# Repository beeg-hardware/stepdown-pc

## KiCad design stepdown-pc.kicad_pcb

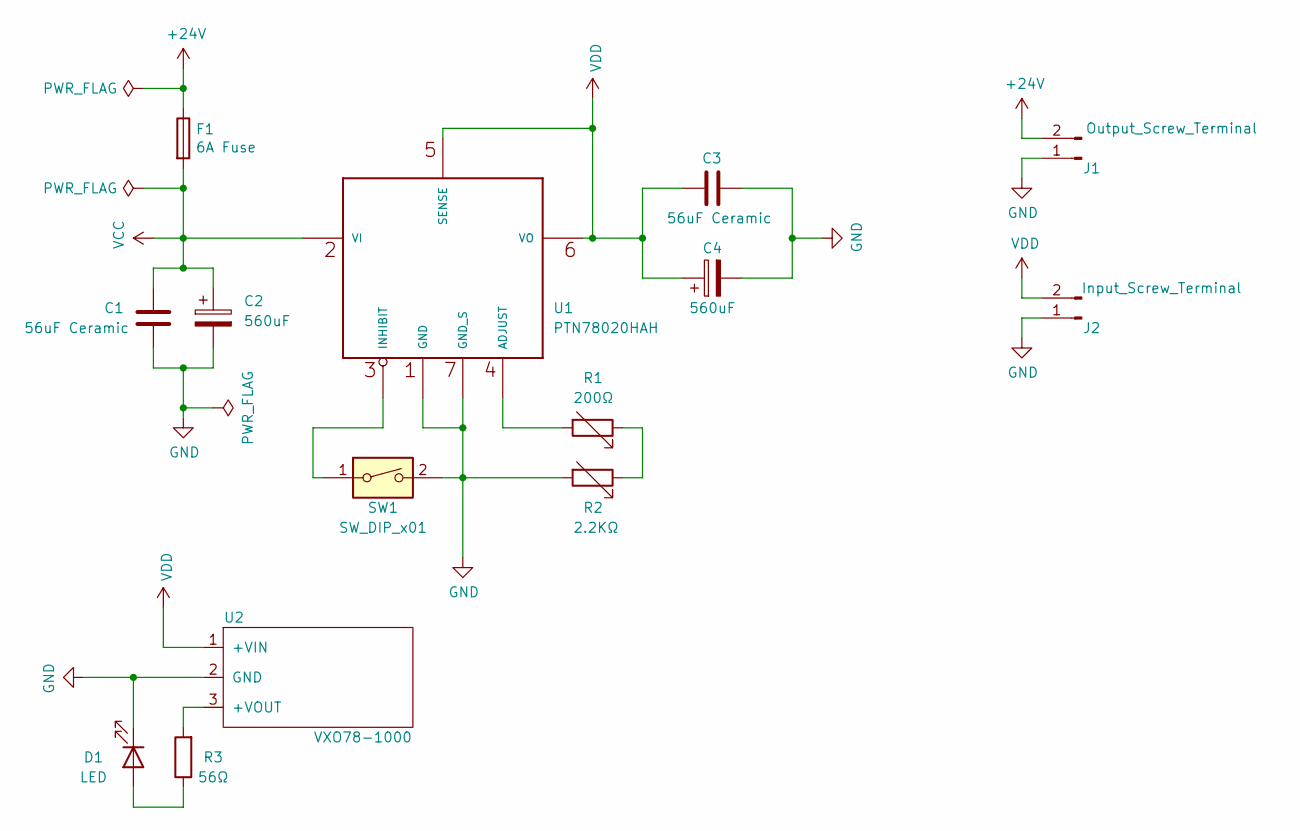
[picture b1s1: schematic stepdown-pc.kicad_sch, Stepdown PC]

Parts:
C1, C3: 56uF Ceramic; C_Rect_L7.0mm_W3.5mm_P5.00mm
C2, C4: 560uF; CP_Radial_D18.0mm_P7.50mm
D1: LED; LED_Rectangular_W3.0mm_H2.0mm
F1: 6A Fuse; Fuseholder_Cylinder-5x20mm_Littlelfuse_520_Horizontal_Open
J1: Output_Screw_Terminal; PhoenixContact_MSTBA_2,5_2-G-5,08_1x02_P5.08mm_Horizontal
J2: Input_Screw_Terminal; PhoenixContact_MSTBA_2,5_2-G-5,08_1x02_P5.08mm_Horizontal
R1: 200Ω; Potentiometer_Piher_Amphenol_PT-10-V10_Vertical_Hole
R2: 2.2KΩ; Potentiometer_Piher_Amphenol_PT-10-V10_Vertical_Hole
R3: 56Ω; R_Axial_DIN0207_L6.3mm_D2.5mm_P10.16mm_Horizontal
SW1: SW_DIP_x01; SW_DIP_SPSTx01_Slide_9.78x4.72mm_W7.62mm_P2.54mm
U1: PTN78020HAH
U2: VXO78-1000

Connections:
+24V: F1.1, J1.2
GND: C1.2, C2.2, C3.2, C4.2, D1.1 (K), J1.1, J2.1, R2.2, SW1.2, U1.1 (GND), U1.7 (GND_S), U2.2 (GND)
unnamed: D1.2 (A), R3.1
unnamed: R1.1, R2.1
unnamed: R1.2, U1.4 (ADJUST)
unnamed: R3.2, U2.3 (+VOUT)
unnamed: SW1.1, U1.3 (INHIBIT)
VCC: C1.1, C2.1, F1.2, U1.2 (VI)
VDD: C3.1, C4.1, J2.2, U1.5 (SENSE), U1.6 (VO), U2.1 (+VIN)

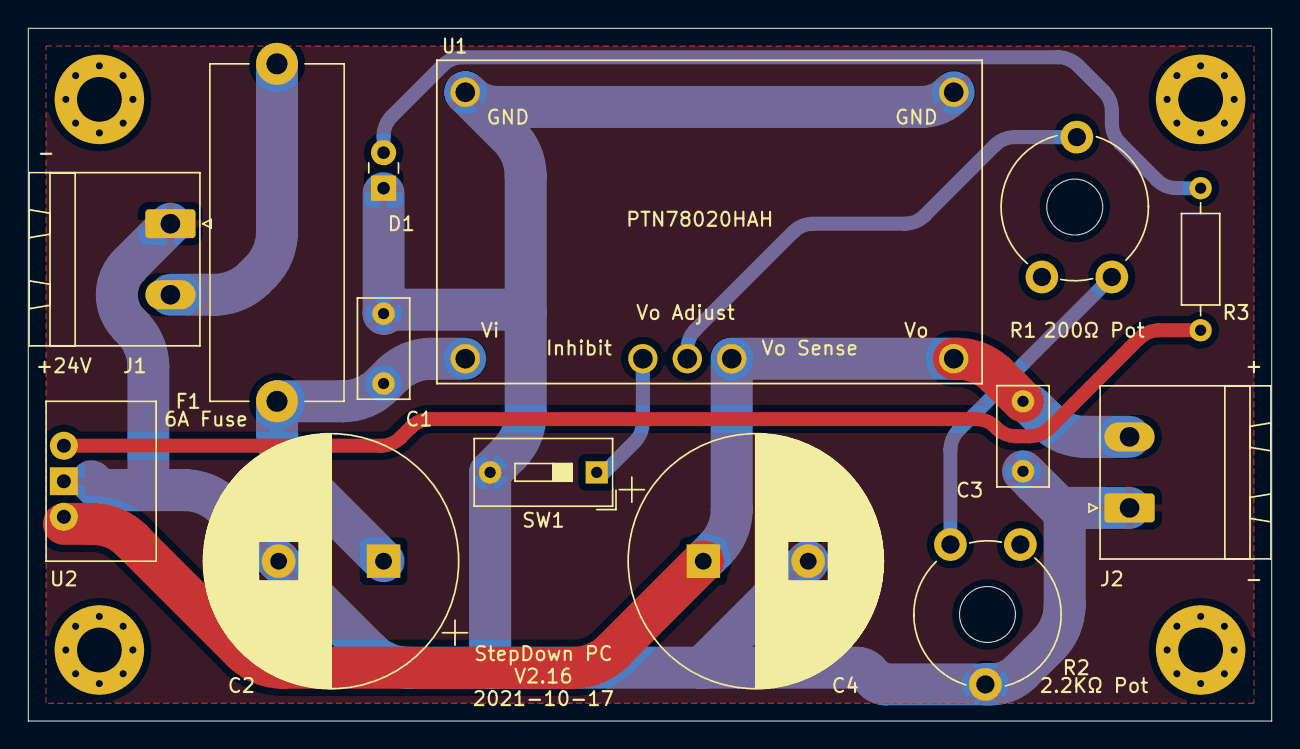
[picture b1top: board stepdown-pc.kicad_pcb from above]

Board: 2 copper layers, 88.9 x 49.5 mm, 18 parts (0 on the bottom side), 9 nets.

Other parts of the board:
H1, H2, H3, H4: MountingHole_3.2mm_M3_Pad_Via

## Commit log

2022-09-27 Import from older project
